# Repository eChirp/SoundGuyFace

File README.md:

# SoundGuyFace
This is a simple USB audio interface using the Texas Instruments 2912A. The IC is a single chip solution for standard audio needs with a computer. Professional microphones use the XLR connector and have differential signals. The SoundGuyFace takes both, microphone and instrument 1/4" cables. A dedicated gain knob let you choose the input sensitivity.

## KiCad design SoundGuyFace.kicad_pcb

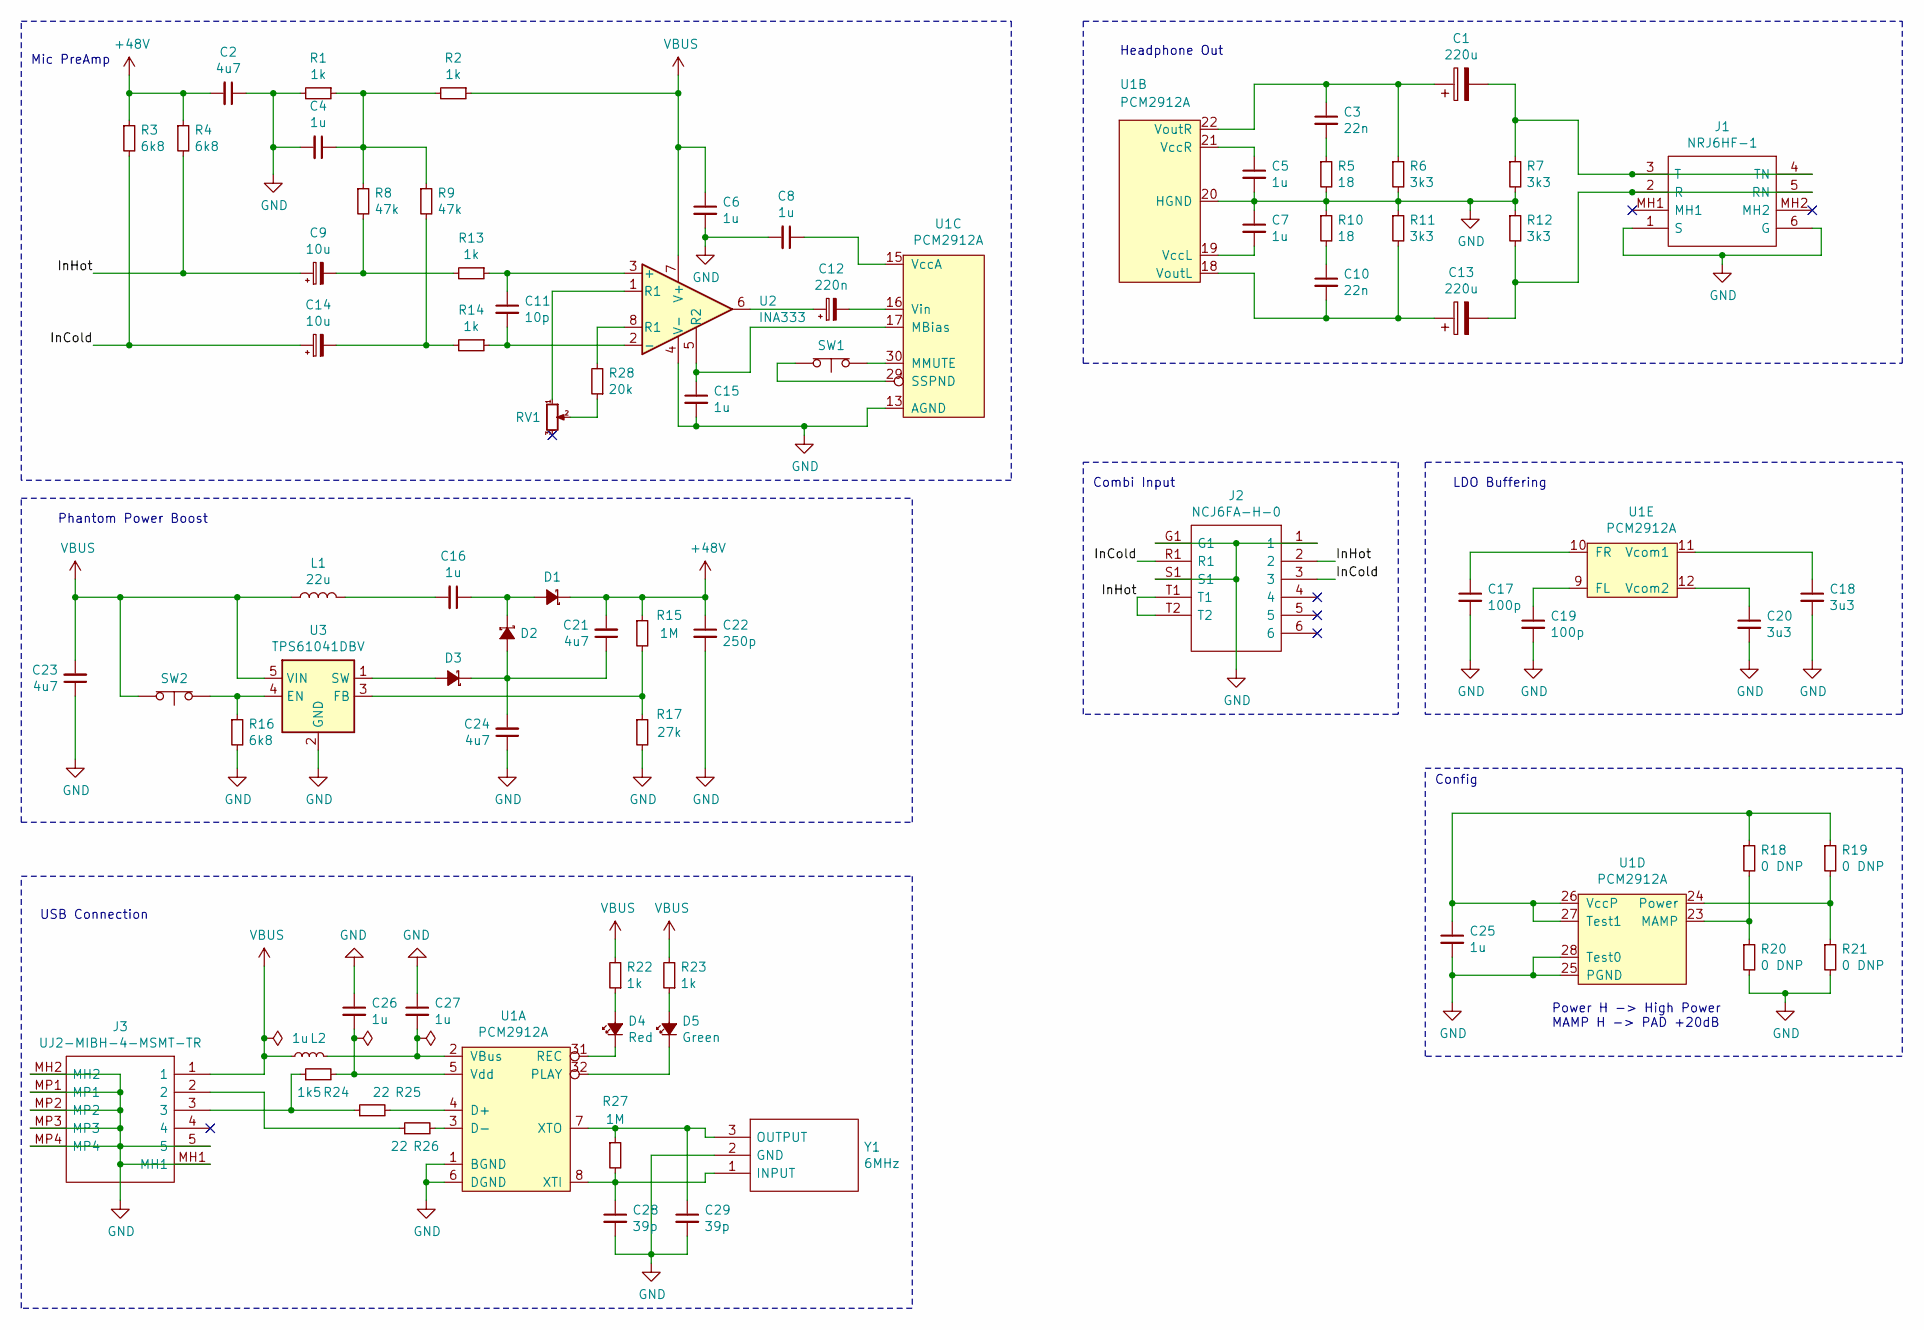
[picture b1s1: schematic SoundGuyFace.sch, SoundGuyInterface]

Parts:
C1, C13: 220u; CP_Radial_D6.3mm_P2.50mm; Manufacturer Part ID 860020373010; Mouser ID 710-860020373010
C2, C21, C23, C24: 4u7; C_0402_1005Metric; Manufacturer Part ID 08055D475KAT2A; Mouser ID 581-08055D475KAT2A
C3, C10: 22n; C_0402_1005Metric; Manufacturer Part ID 885012205052; Mouser ID 710-885012205052
C4, C5, C6, C7, C8, C15, C25, C26, C27: 1u; C_0402_1005Metric; Manufacturer Part ID LMK105BJ105MVHF; Mouser ID 963-LMK105BJ105MVHF
C9, C14: 10u; CP_Radial_D5.0mm_P2.00mm; Manufacturer Part ID 860020772010; Mouser ID 710-860020772010
C11: 10p; C_0402_1005Metric; Manufacturer Part ID 885012005007; Mouser ID 710-885012005007
C12: 220n; CP_Radial_D5.0mm_P2.00mm; Manufacturer Part ID 860010672002; Mouser ID 710-860010672002
C16: 1u; C_0805_2012Metric; Manufacturer Part ID UMK212BJ105MG-T; Mouser ID 963-UMK212BJ105MG-T
C17, C19: 100p; C_0402_1005Metric; Manufacturer Part ID 885012005013; Mouser ID 710-885012005013
C18, C20: 3u3; C_0402_1005Metric; Manufacturer Part ID C1005X5R1A335K050BC; Mouser ID 810-C1005X5R1A335K0C
C22: 250p; C_0603_1608Metric; Manufacturer Part ID 0603N251J500CT; Mouser ID 791-0603N251J500CT
C28, C29: 39p; C_0402_1005Metric; Manufacturer Part ID C0402C390J5GACTU; Mouser ID 80-C0402C390J5G
D1, D2, D3: D_Schottky_Small_ALT; D_SMA_Handsoldering; Manufacturer Part ID FM5819-W; Mouser ID 583-FM5819
D4: Red; D_1210_3225Metric; Manufacturer Part ID AA3021ES; Mouser ID 604-AA3021ES
D5: Green; D_1210_3225Metric; Manufacturer Part ID AA3021SGS; Mouser ID 604-AA3021SGS
J1: NRJ6HF-1; NRJ6HF1; Mouser Part Number 550-20384
J2: NCJ6FA-H-0; NCJ6FAH0; Mouser Part Number 568-NCJ6FA-H-0
J3: UJ2-MIBH-4-MSMT-TR; UJ2MIBH4MSMTTR; Mouser Part Number 490-UJ2-MIBH-4-MSMT
L1: 22u; INDPM6060X450N; Manufacturer Part ID 74404064220; Mouser ID 710-74404064220
L2: 1u; L_0805_2012Metric; Manufacturer Part ID 74479276210C; Mouser ID 710-74479276210C
R1, R2, R13, R14, R22, R23: 1k; R_0402_1005Metric; Manufacturer Part ID CRCW04021K00FKEDC; Mouser ID 71-CRCW04021K00FKEDC
R3, R4, R16: 6k8; R_0402_1005Metric; Manufacturer Part ID CRCW04026K80FKED; Mouser ID 71-CRCW04026K80FKED
R5, R10: 18; R_0402_1005Metric; Manufacturer Part ID ERJ2RKD18R0X; Mouser ID 667-ERJ-2RKD18R0X
R6, R7, R11, R12: 3k3; R_0402_1005Metric; Manufacturer Part ID SFR01MZPF3301; Mouser ID 755-SFR01MZPF3301
R8, R9: 47k; R_0402_1005Metric; Manufacturer Part ID CRCW040247K0FKEDC; Mouser ID 71-CRCW040247K0FKEDC
R15, R27: 1M; R_0402_1005Metric; Manufacturer Part ID SFR01MZPJ105; Mouser ID 755-SFR01MZPJ105
R17: 27k; R_0402_1005Metric; Manufacturer Part ID SFR01MZPF2702; Mouser ID 755-SFR01MZPF2702
R18, R19, R20, R21: 0 DNP; R_0201_0603Metric
R24: 1k5; R_0402_1005Metric; Manufacturer Part ID RC0100JR-071K5L; Mouser ID 603-RC0100JR-071K5L
R25, R26: 22; R_0402_1005Metric; Manufacturer Part ID SFR01MZPF22R0; Mouser ID 755-SFR01MZPF22R0
R28: 20k; R_0402_1005Metric; Manufacturer Part ID CRCW040220K0FKEDC; Mouser ID 71-CRCW040220K0FKEDC
RV1: R_POT_Small; Potentiometer_Alps_RK097_Dual_Horizontal
SW1, SW2: SW_Push_Open; PinHeader_1x02_P2.54mm_Vertical
U1: PCM2912A; TQFP-32_7x7mm_P0.8mm
U2: INA333; VSSOP-8_3.0x3.0mm_P0.65mm; Manufacturer Part ID INA333AIDGKR; Mouser ID 595-INA333AIDGKR
U3: TPS61041DBV; SOT-23-5; Manufacturer Part ID TPS61040DBVR; Mouser ID 595-TPS61040DBVR
Y1: 6MHz; CSTNR6M00GH5L000R0; Mouser Part Number 81-CSTNR6M00GH5L000R

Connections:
+48V: C2.2, C21.2, C22.1, D1.1 (K), R3.1, R4.1, R15.1
/InCold: C14.1, J2.3, J2.R1, R3.2
/InHot: C9.1, J2.2, J2.T1, J2.T2, R4.2
GND: C2.1, C4.2, C5.2, C6.2, C7.1, C8.2, C15.2, C17.2, C18.2, C19.2, C20.2, C22.2, C23.1, C24.1, C25.2, C26.1, C27.1, C28.2, C29.2, J1.1 (S), J1.6 (G), J2.1, J2.G1, J2.S1, J3.5, J3.MH1, J3.MH2, J3.MP1, J3.MP2, J3.MP3, J3.MP4, R1.2, R5.2, R6.2, R7.2, R10.1, R11.1, R12.1, R16.2, R17.2, R20.2, R21.2, U1.1 (BGND), U1.6 (DGND), U1.13 (AGND), U1.20 (HGND), U1.25 (PGND), U1.28 (Test0), U2.4 (V-), U3.2 (GND), Y1.2 (GND)
unnamed: C1.1, C3.1, R6.1, U1.22 (VoutR)
unnamed: C1.2, J1.3 (T), J1.4 (TN), R7.1
unnamed: C3.2, R5.1
unnamed: C4.1, R1.1, R2.2, R8.1, R9.1
unnamed: C5.1, U1.21 (VccR)
unnamed: C7.2, U1.19 (VccL)
unnamed: C8.1, U1.15 (VccA)
unnamed: C9.2, R8.2, R13.2
unnamed: C10.1, R10.2
unnamed: C10.2, C13.1, R11.2, U1.18 (VoutL)
unnamed: C11.1, R13.1, U2.3 (+)
unnamed: C11.2, R14.1, U2.2 (-)
unnamed: C12.1, U2.6
unnamed: C12.2, U1.16 (Vin)
unnamed: C13.2, J1.2 (R), J1.5 (RN), R12.2
unnamed: C14.2, R9.2, R14.2
unnamed: C15.1, U1.17 (MBias), U2.5 (R2)
unnamed: C16.1, D1.2 (A), D2.1 (K)
unnamed: C16.2, L1.2
unnamed: C17.1, U1.10 (FR)
unnamed: C18.1, U1.11 (Vcom1)
unnamed: C19.1, U1.9 (FL)
unnamed: C20.1, U1.12 (Vcom2)
unnamed: C21.1, C24.2, D2.2 (A), D3.1 (K)
unnamed: C25.1, R18.1, R19.1, U1.26 (VccP), U1.27 (Test1)
unnamed: C26.2, R24.2, U1.5 (Vdd)
unnamed: C27.2, L2.2, U1.2 (VBus)
unnamed: C28.1, R27.2, U1.8 (XTI), Y1.1 (INPUT)
unnamed: C29.1, R27.1, U1.7 (XTO), Y1.3 (OUTPUT)
unnamed: D3.2 (A), U3.1 (SW)
unnamed: D4.1 (K), U1.31 (REC)
unnamed: D4.2 (A), R22.1
unnamed: D5.1 (K), U1.32 (PLAY)
unnamed: D5.2 (A), R23.1
unnamed: J3.2, R26.1
unnamed: J3.3, R24.1, R25.1
unnamed: R15.2, R17.1, U3.3 (FB)
unnamed 47: R16.1, SW2.2 (B), U3.4 (EN); also elsewhere on the board
unnamed: R18.2, R20.1, U1.23 (MAMP)
unnamed: R19.2, R21.1, U1.24 (Power)
unnamed: R25.2, U1.4 (D+)
unnamed: R26.2, U1.3 (D-)
unnamed: R28.1, RV1.2
unnamed: R28.2, U2.8 (R1)
unnamed: RV1.1, U2.1 (R1)
unnamed 56: SW1.1 (A), U1.29 (SSPND); also elsewhere on the board
unnamed 57: SW1.2 (B), U1.30 (MMUTE); also elsewhere on the board
VBUS: C6.1, C23.2, J3.1, L1.1, L2.1, R2.1, R22.2, R23.2, SW2.1 (A), U2.7 (V+), U3.5 (VIN); also elsewhere on the board

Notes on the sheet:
Power H -> High Power MAMP H -> PAD +20dB
LDO Buffering
Headphone Out
Config
Mic PreAmp
USB Connection
Combi Input
Phantom Power Boost

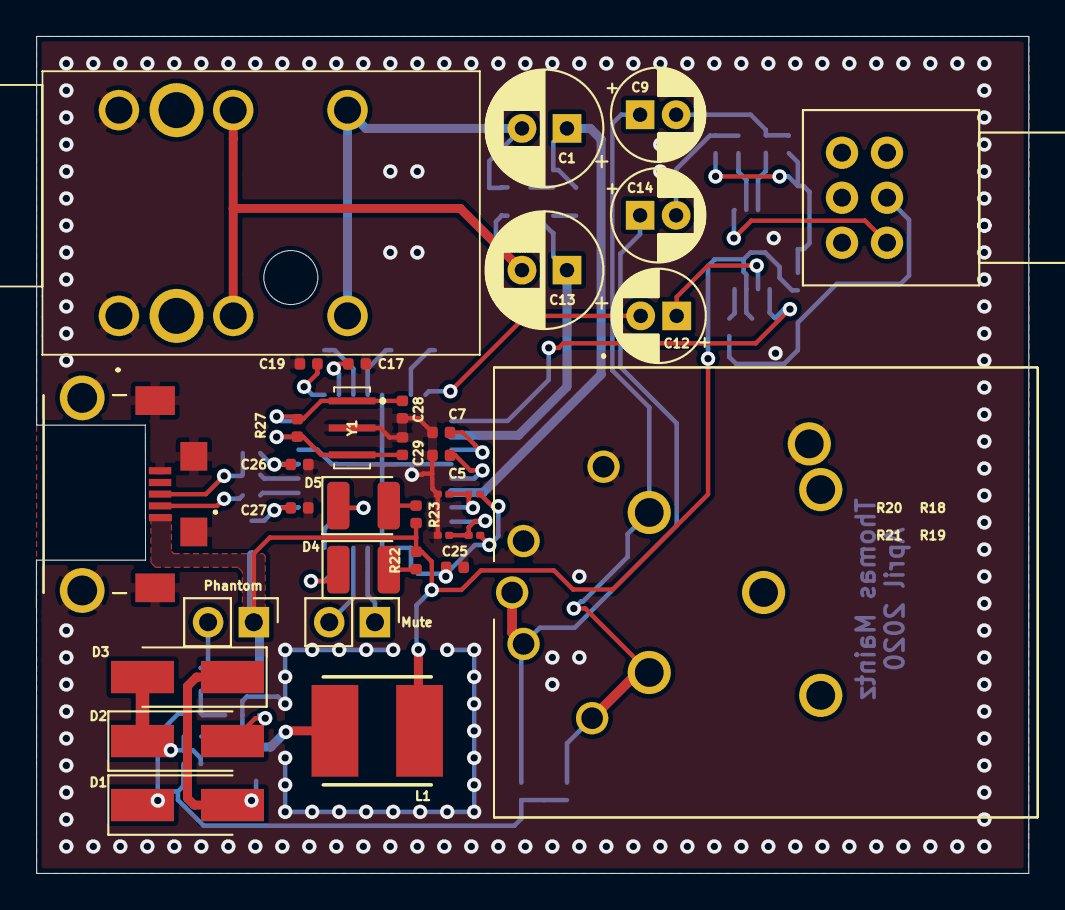
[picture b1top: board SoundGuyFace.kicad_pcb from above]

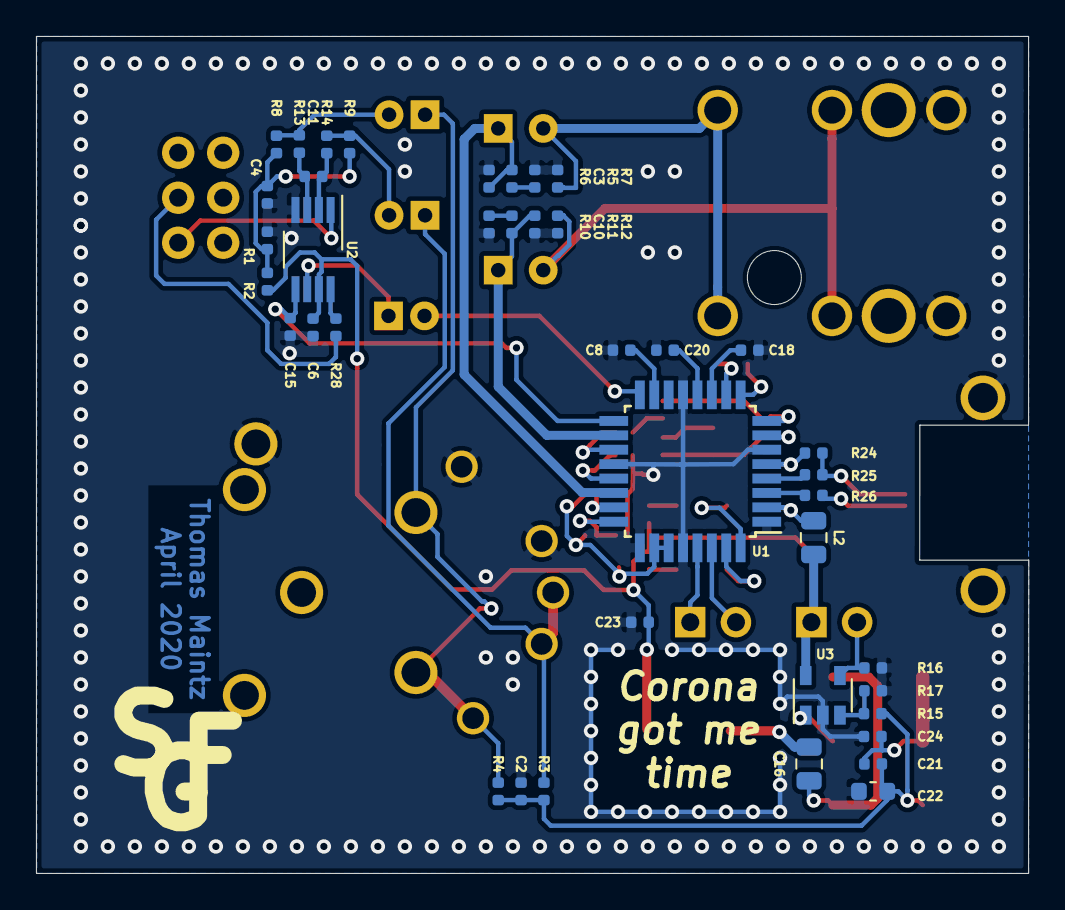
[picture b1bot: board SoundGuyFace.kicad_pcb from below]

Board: 2 copper layers, 55.1 x 46.5 mm, 74 parts (40 on the bottom side), 52 nets.

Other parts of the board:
Mute: SW_Push_Open; PinHeader_1x02_P2.54mm_Vertical
Phantom: SW_Push_Open; PinHeader_1x02_P2.54mm_Vertical

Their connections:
unnamed 47: Phantom.2; also elsewhere on the board
unnamed 56: Mute.1; also elsewhere on the board
unnamed 57: Mute.2; also elsewhere on the board
VBUS: Phantom.1; also elsewhere on the board

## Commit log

2020-05-09 Extended gitignore
2020-05-09 Added project specific libraries
2020-05-09 Simulation models for TINA simulator added
2020-05-09 Initial KiCAD project commit
2020-05-10 Small schematic changes and first PCB layout done
2020-05-10 Added initial BOM
2020-05-10 Version to dispatch
2020-05-15 First Hardware debug. Forgot sparing for the USB connector
2020-05-22 Added outline for USB part
